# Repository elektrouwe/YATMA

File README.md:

# YATMA
//---------------------------------------------------------------------------------------------------------

Yet Another Transitor MAtcher

//---------------------------------------------------------------------------------------------------------

read this thread for more information :
https://www.muffwiggler.com/forum/viewtopic.php?f=17&t=153845

here you can find KICAD and fabrication files

//---------------------------------------------------------------------------------------------------------

update Nov.26. 2020:
YATMA2 folder uploaded. KICAD files have been made with an old version; may need changes to work with current KICAD version - not tested. 

For the same reason I did not upload original YATMA KICAD files. They are even older and used now obsolete
libraries. Feel free to draw them again from the PDFs and upload them here, TIA elektrouwe :-)

//---------------------------------------------------------------------------------------------------------

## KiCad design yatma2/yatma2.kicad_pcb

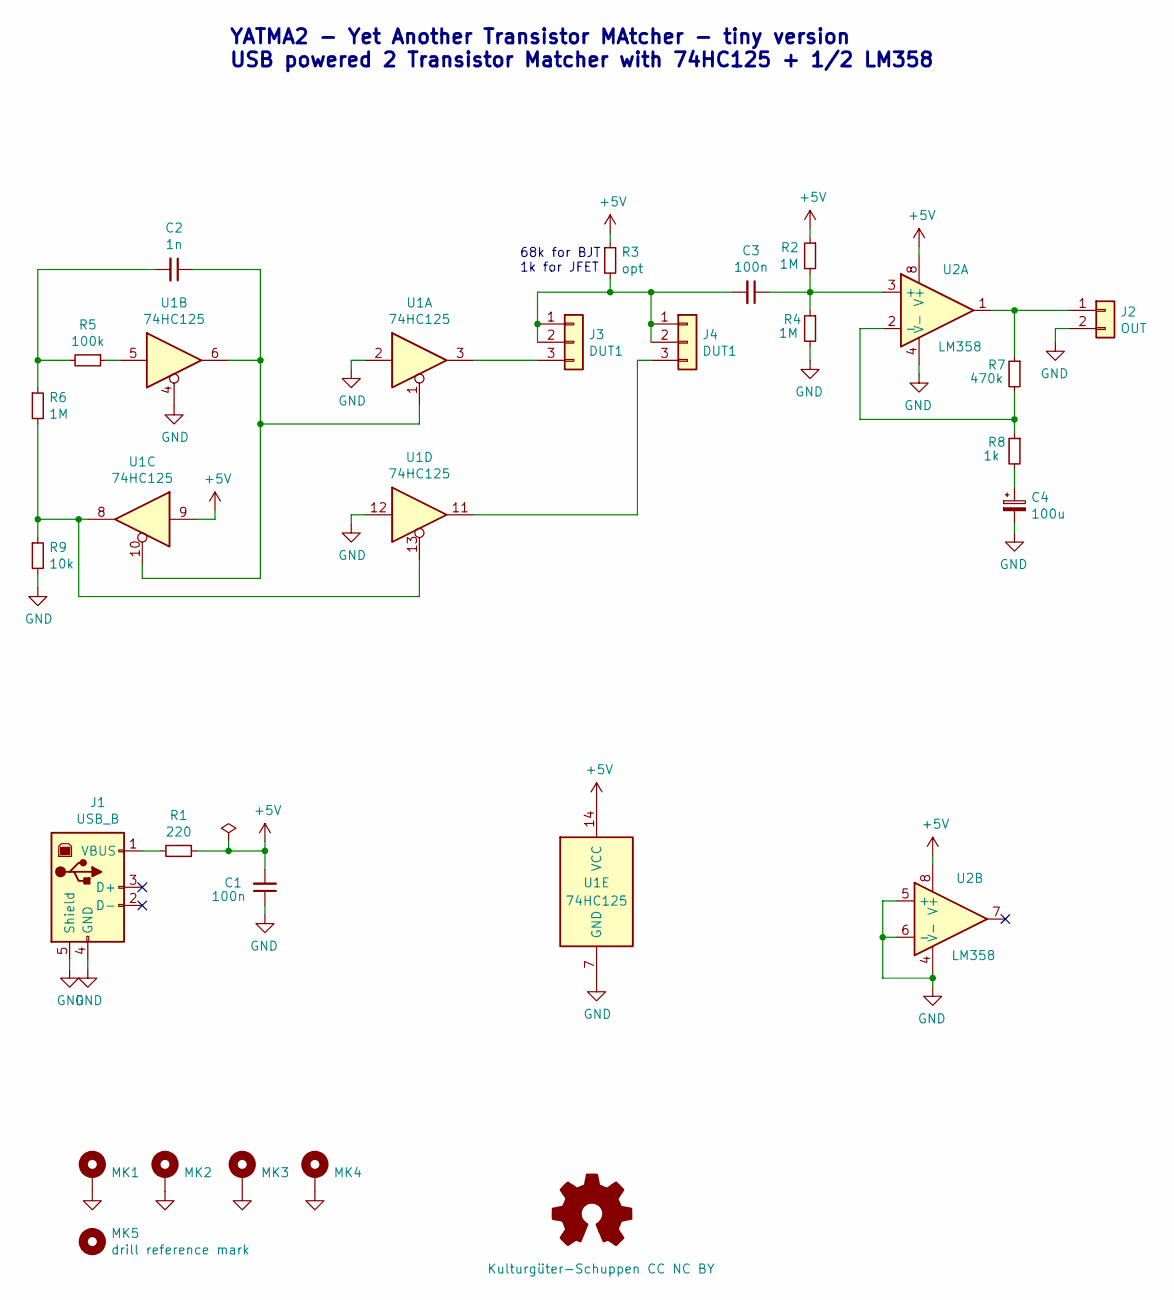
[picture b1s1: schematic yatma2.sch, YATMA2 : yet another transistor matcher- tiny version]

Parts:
C1, C3: 100n; C_Disc_D7.5mm_W5.0mm_P5.00mm
C2: 1n; C_Disc_D7.5mm_W5.0mm_P5.00mm
C4: 100u; CP_Radial_D10.0mm_P5.00mm
J1: USB_B; USB_B_Horizontal
J2: OUT; PinHeader_1x02_P2.54mm_Vertical
J3, J4: DUT1; PinHeader_1x03_P2.54mm_Vertical
MK1, MK2, MK3, MK4: Mounting_Hole_PAD; MountingHole_3.2mm_M3_DIN965
MK5: drill reference mark; TestPoint_THTPad_D1.0mm_Drill0.5mm
R1: 220; R_Axial_DIN0207_L6.3mm_D2.5mm_P10.16mm_Horizontal
R2, R4, R6: 1M; R_Axial_DIN0207_L6.3mm_D2.5mm_P10.16mm_Horizontal
R3: opt; R_Axial_DIN0207_L6.3mm_D2.5mm_P10.16mm_Horizontal
R5: 100k; R_Axial_DIN0207_L6.3mm_D2.5mm_P10.16mm_Horizontal
R7: 470k; R_Axial_DIN0207_L6.3mm_D2.5mm_P10.16mm_Horizontal
R8: 1k; R_Axial_DIN0207_L6.3mm_D2.5mm_P10.16mm_Horizontal
R9: 10k; R_Axial_DIN0207_L6.3mm_D2.5mm_P10.16mm_Horizontal
U1: 74HC125; DIP-14_W7.62mm_Socket_LongPads
U2: LM358

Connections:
+5V: C1.2, R1.1, R2.1, R3.1, U1.9, U1.14 (VCC), U2.8 (V+)
GND: C1.1, C4.2, J1.4 (GND), J1.5 (Shield), J2.2, MK1.1, MK2.1, MK3.1, MK4.1, R4.2, R9.2, U1.2, U1.4, U1.7 (GND), U1.12, U2.4 (V-), U2.5 (+), U2.6 (-)
unnamed: C2.1, U1.1, U1.6, U1.10
unnamed: C2.2, R5.2, R6.1
unnamed: C3.1, R2.2, R4.1, U2.3 (+)
unnamed: C3.2, J3.1, J3.2, J4.1, J4.2, R3.2
unnamed: C4.1, R8.2
unnamed: J1.1 (VBUS), R1.2
unnamed: J2.1, R7.1, U2.1
unnamed: J3.3, U1.3
unnamed: J4.3, U1.11
unnamed: R5.1, U1.5
unnamed: R6.2, R9.1, U1.8, U1.13
unnamed: R7.2, R8.1, U2.2 (-)

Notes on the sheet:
YATMA2 - Yet Another Transistor MAtcher - tiny version USB powered 2 Transistor Matcher with 74HC125 + 1/2 LM358
68k for BJT 1k for JFET

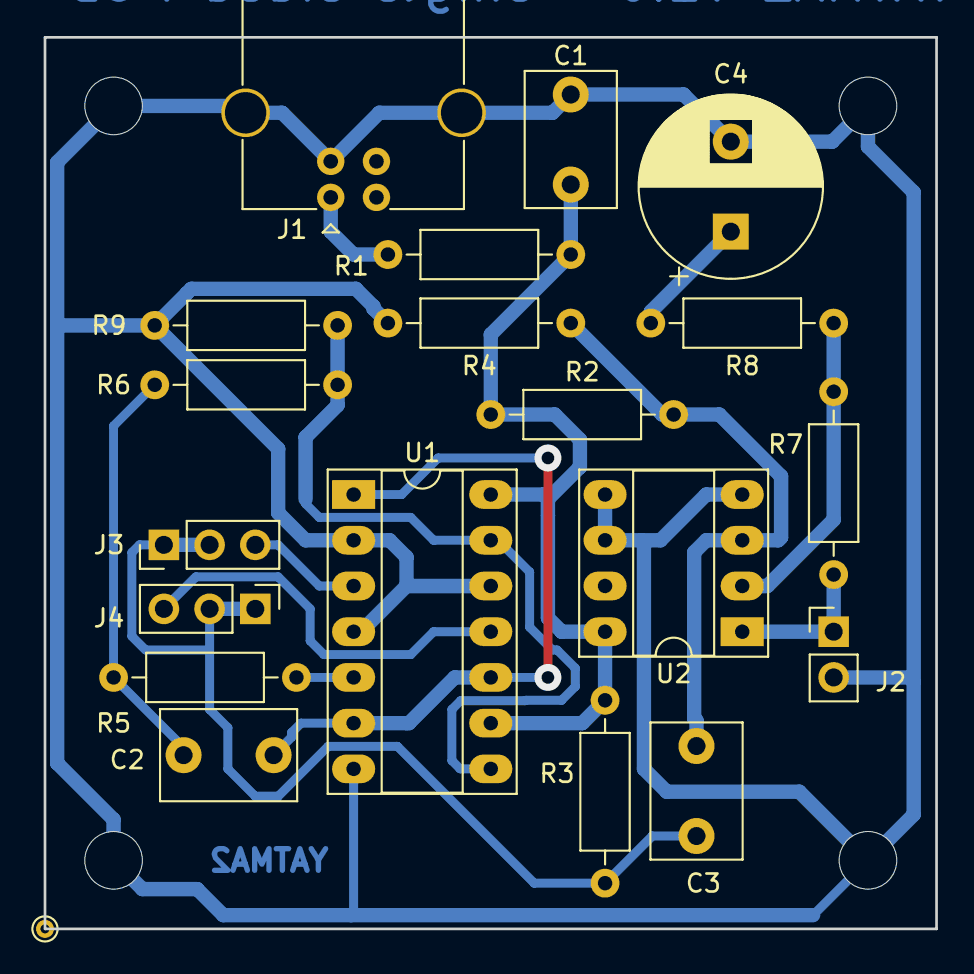
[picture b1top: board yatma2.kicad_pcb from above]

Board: 2 copper layers, 49.5 x 49.5 mm, 24 parts (0 on the bottom side), 14 nets.

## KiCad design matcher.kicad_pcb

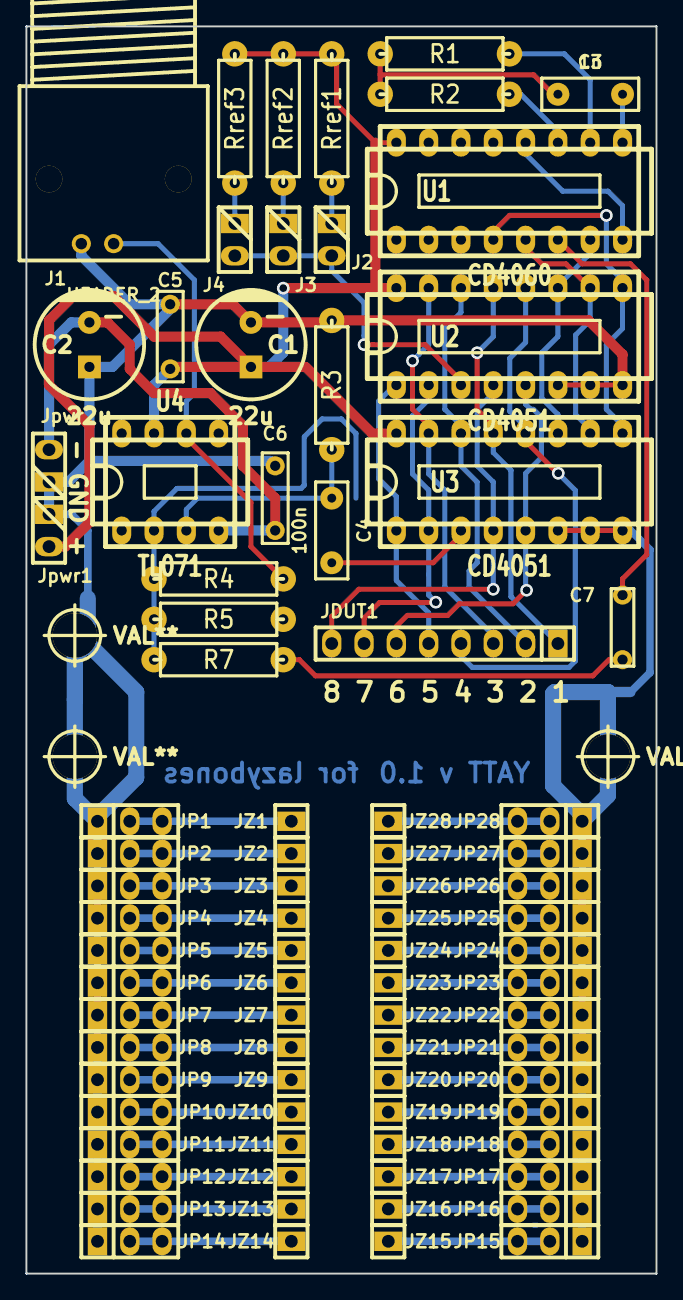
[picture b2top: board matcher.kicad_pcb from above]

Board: 2 copper layers, 49.5 x 98.0 mm, 86 parts (0 on the bottom side), 56 nets.

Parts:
C1, C2: 22u; CP_8x11.5mm
C3: 1n; cnp_7x3mm
C4: 100n; cnp_7x3mm
C5, C6: 100n; cnp_7.5mm_disc
C7: 100p..1n; cnp_6mm_disc
J1: HEADER_2; bnc_90_1-1337543-0
J2, J3, J4: HEADER_2; pin_strip_2
JDUT1: HEADER_8; pin_strip_8
JP1, JP2, JP3, JP4, JP5, JP6, JP7, JP8, JP9, JP10, JP11, JP12, JP13, JP14, JP15, JP16, JP17, JP18, JP19, JP20, JP21, JP22, JP23, JP24, JP25, JP26, JP27, JP28: HEADER_3; pin_strip_3
JZ1, JZ2, JZ3, JZ4, JZ5, JZ6, JZ7, JZ8, JZ9, JZ10, JZ11, JZ12, JZ13, JZ14, JZ15, JZ16, JZ17, JZ18, JZ19, JZ20, JZ21, JZ22, JZ23, JZ24, JZ25, JZ26, JZ27, JZ28: HEADER_1; pin_strip_1
Jpwr1, Jpwr2: HEADER_2; pin_strip_2
R1, R2, R7: 47k; RC05
R3: 1M; RC05
R4: 100k; RC05
R5: 100; RC05
Rref1: 6k8; RC05
Rref2: 68k; RC05
Rref3: 680k; RC05
U1: CD4060; dil_16-300_socket
U2, U3: CD4051; dil_16-300_socket
U4: TL071; dil_8-300_socket
hole_3mm5, hole_3mm5#2, hole_3mm5#3: VAL**; hole_3mm5

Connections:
/-12V: C2.2, C6.2, Jpwr2.2, U4.4
/a0: U1.7, U2.11, U3.11
/a1: U1.5, U2.10, U3.10
/a2: U1.4, U2.9, U3.9
/trigger: C7.2, U1.6
GND: C1.2, C2.1, C5.1, C6.1, J1.2, JP1.1, JP2.1, JP3.1, JP4.1, JP5.1, JP6.1, JP7.1, JP8.1, JP9.1, JP10.1, JP11.1, JP12.1, JP13.1, JP14.1, JP15.1, JP16.1, JP17.1, JP18.1, JP19.1, JP20.1, JP21.1, JP22.1, JP23.1, JP24.1, JP25.1, JP26.1, JP27.1, JP28.1, Jpwr1.1, Jpwr2.1, R3.2, R5.2, U1.8, U1.12, U2.6, U2.7, U2.8, U3.6, U3.7, U3.8, hole_3mm5.1, hole_3mm5#2.1, hole_3mm5#3.1
unnamed: C3.1, U1.9
unnamed: C3.2, R1.2, R2.2
unnamed: C4.1, R3.1, U4.3
unnamed: C4.2, U3.3
unnamed: C7.1, R7.2
unnamed: J1.1, R4.1, U4.6
unnamed: J2.1, Rref1.2
unnamed: J2.2, J3.2, J4.2, U2.3
unnamed: J3.1, Rref2.2
unnamed: J4.1, Rref3.2
unnamed: JDUT1.1, U2.13, U3.13
unnamed: JDUT1.2, U2.14, U3.14
unnamed: JDUT1.3, U2.15, U3.15
unnamed: JDUT1.4, U2.12, U3.12
unnamed: JDUT1.5, U2.1, U3.1
unnamed: JDUT1.6, U2.5, U3.5
unnamed: JDUT1.7, U2.2, U3.2
unnamed: JDUT1.8, U2.4, U3.4
unnamed: JP1.2, JP1.3, JZ1.1
unnamed: JP2.2, JP2.3, JZ2.1
unnamed: JP3.2, JP3.3, JZ3.1
unnamed: JP4.2, JP4.3, JZ4.1
unnamed: JP5.2, JP5.3, JZ5.1
unnamed: JP6.2, JP6.3, JZ6.1
unnamed: JP7.2, JP7.3, JZ7.1
unnamed: JP8.2, JP8.3, JZ8.1
unnamed: JP9.2, JP9.3, JZ9.1
unnamed: JP10.2, JP10.3, JZ10.1
unnamed: JP11.2, JP11.3, JZ11.1
unnamed: JP12.2, JP12.3, JZ12.1
unnamed: JP13.2, JP13.3, JZ13.1
unnamed: JP14.2, JP14.3, JZ14.1
unnamed: JP15.2, JP15.3, JZ15.1
unnamed: JP16.2, JP16.3, JZ16.1
unnamed: JP17.2, JP17.3, JZ17.1
unnamed: JP18.2, JP18.3, JZ18.1
unnamed: JP19.2, JP19.3, JZ19.1
unnamed: JP20.2, JP20.3, JZ20.1
unnamed: JP21.2, JP21.3, JZ21.1
unnamed: JP22.2, JP22.3, JZ22.1
unnamed: JP23.2, JP23.3, JZ23.1
unnamed: JP24.2, JP24.3, JZ24.1
unnamed: JP25.2, JP25.3, JZ25.1
unnamed: JP26.2, JP26.3, JZ26.1
unnamed: JP27.2, JP27.3, JZ27.1
unnamed: JP28.2, JP28.3, JZ28.1
unnamed: R1.1, U1.10
unnamed: R2.1, U1.11
unnamed: R4.2, R5.1, R7.1, U4.2
VDD: C1.1, C5.2, Jpwr1.2, Rref1.1, Rref2.1, Rref3.1, U1.16, U2.16, U3.16, U4.7
